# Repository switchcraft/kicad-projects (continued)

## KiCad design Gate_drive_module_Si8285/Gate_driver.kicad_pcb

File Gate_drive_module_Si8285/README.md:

# Gate driver plug-in module Si8285 edition

Gate driver plug-in module for use as a plug-in component on any circuit board
that needs to drive a IGBT, MOSFET, or SiC power transistor.

The Si8285 is a relatively cheap advanced gate drive IC.

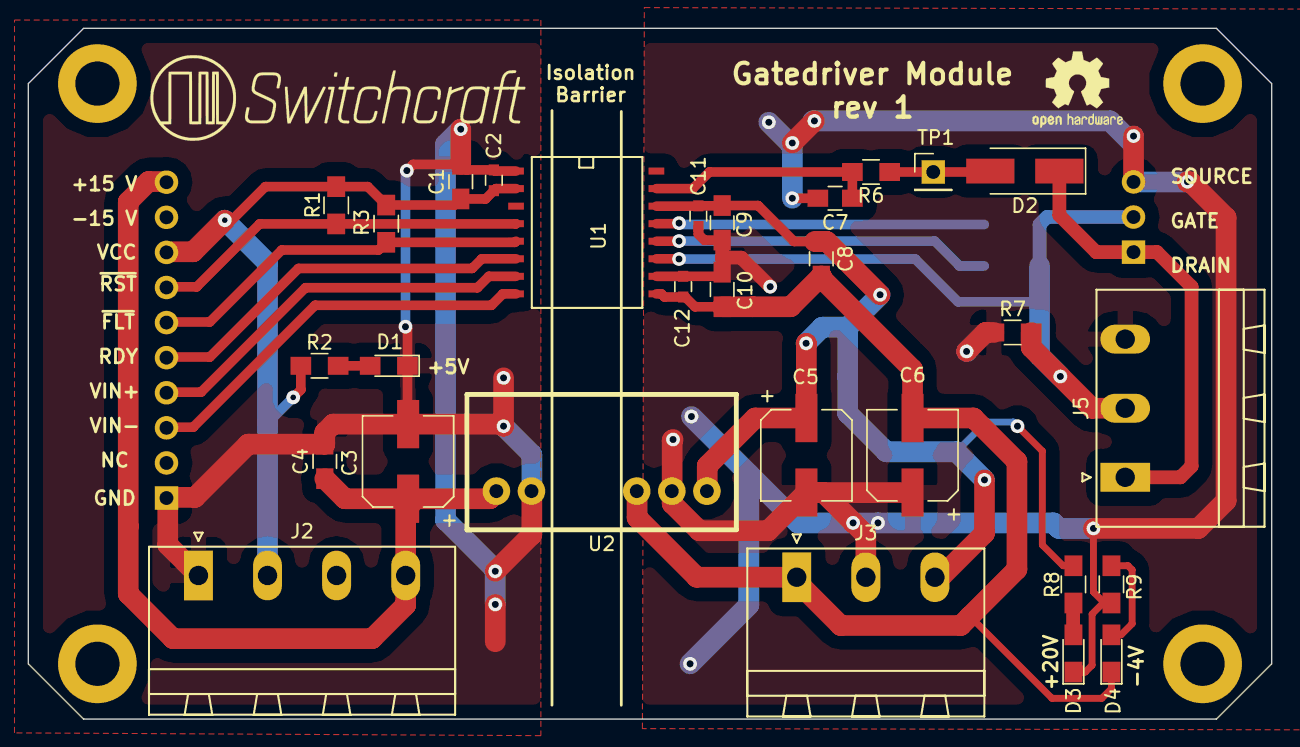
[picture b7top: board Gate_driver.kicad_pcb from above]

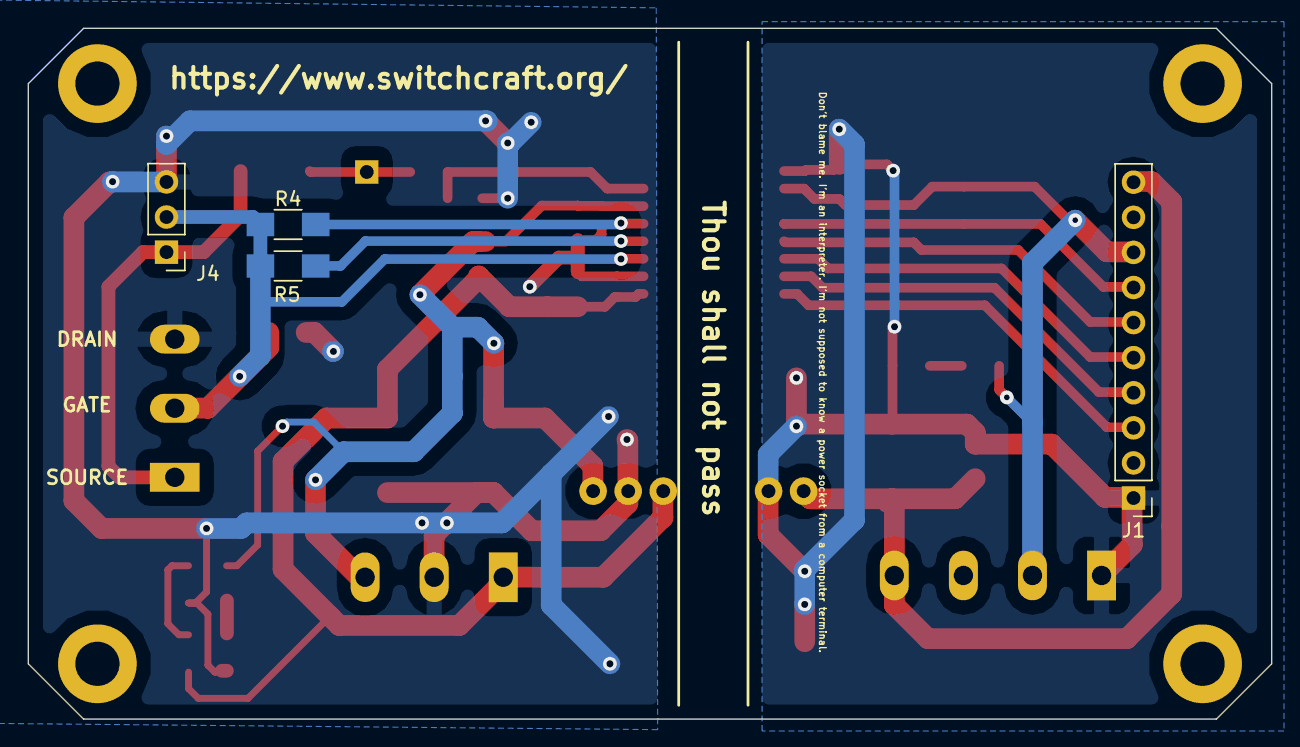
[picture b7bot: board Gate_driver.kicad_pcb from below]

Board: 2 copper layers, 90.0 x 50.0 mm, 33 parts (4 on the bottom side), 20 nets.

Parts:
C1, C8, C9, C10: 10u; C_0805_HandSoldering
C2, C11, C12: 100n; C_0603
C3, C5, C6: 100u; CP_Elec_6.3x7.7
C4: 100n; C_0805_HandSoldering
C7: 390p; C_0805_HandSoldering
D1: RED PWR LED; LED_0805_HandSoldering
D2: ES1F; D_SMA_Handsoldering
D3, D4: GREEN PWR LED; LED_0805_HandSoldering
J1: CONN_01X10; Pin_Header_Straight_1x10_Pitch2.54mm
J2: CONN_01X04; MSTBA_25_4p_G_508-1757268
J3, J5: CONN_01X03; MSTBA_25_3p_G_508-1757488
J4: CONN_01X03; Pin_Header_Straight_1x03_Pitch2.54mm
R1, R2, R3, R8, R9: 10k; R_0805_HandSoldering
R4, R5: 10R; R_1206_HandSoldering
R6: 100R; R_0805_HandSoldering
R7: 100k; R_0805_HandSoldering
TP1: TEST; Pin_Header_Straight_1x01_Pitch2.54mm
U1: Si8285; SO-16-W
U2: Mornsun_QA01C; QA01C

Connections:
+15V: C3.1, C4.1, J1.10, J2.4, U2.1
GND: C1.2, C2.2, C3.2, C4.2, D1.1, J1.1, J2.1, U1.1, U2.2
GND_ISO: C5.2, C6.1, C7.2, C9.2, C10.1, C11.2, C12.1, D3.1, J3.2, J4.3, J5.3, R7.1, R9.1, U1.10, U2.6
unnamed: C7.1, R6.2, U1.15
unnamed: D1.2, R2.2
unnamed: D2.1, J4.1, J5.1
unnamed: D2.2, R6.1, TP1.1
unnamed: D3.2, R8.2
unnamed: D4.2, R9.2
unnamed: J1.3, U1.8
unnamed: J1.4, U1.7
unnamed: J1.5, U1.6
unnamed: J1.6, R3.2, U1.5
unnamed: J1.7, R1.2, U1.4
unnamed: J4.2, J5.2, R4.1, R5.1, R7.2, U1.11
unnamed: R4.2, U1.13
unnamed: R5.2, U1.12
VCC: C1.1, C2.1, J1.8, J2.2, R1.1, R2.1, R3.1, U1.2
VCC_ISO: C5.1, C8.1, C9.1, C11.1, J3.3, R8.1, U1.14, U2.7
VEE_ISO: C6.2, C8.2, C10.2, C12.2, D4.1, J3.1, U1.9, U2.5

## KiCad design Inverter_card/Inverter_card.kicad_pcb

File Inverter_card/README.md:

# Inverter_card

Card for Semikron transistor module card. 

Features connections to gatedrivers and motor output.

This card is designed to sit on top of the DC-link capacitors.

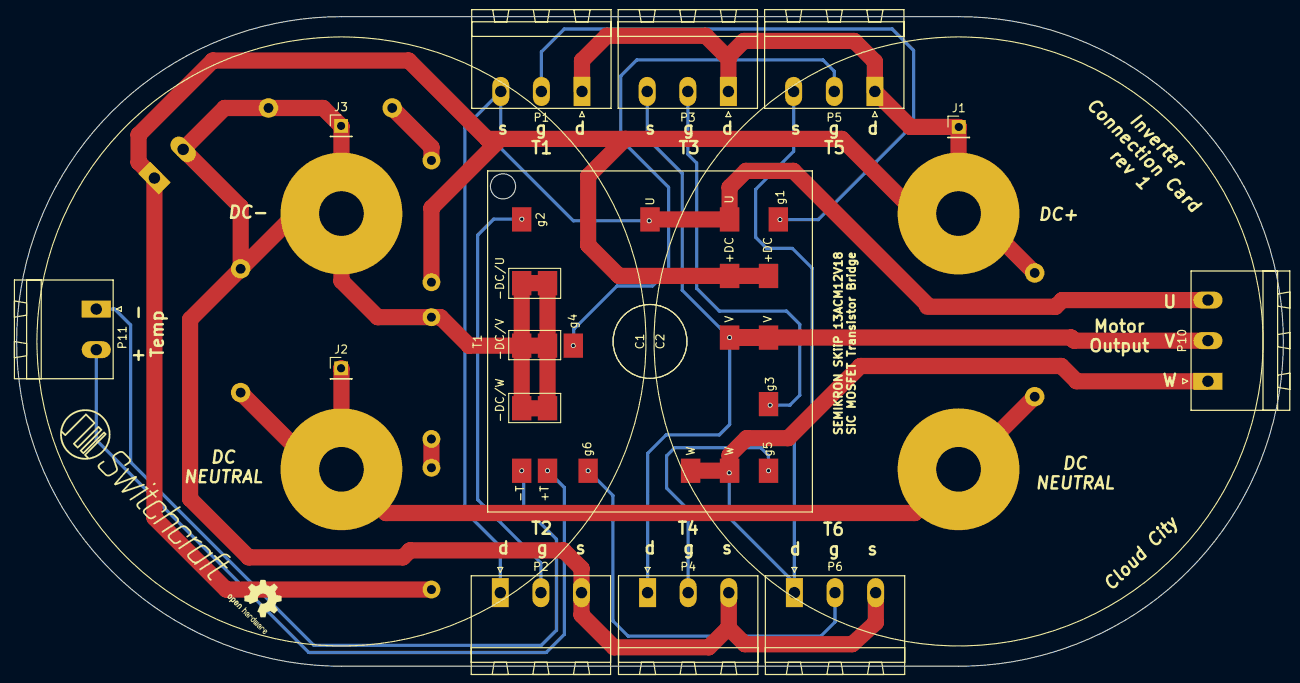
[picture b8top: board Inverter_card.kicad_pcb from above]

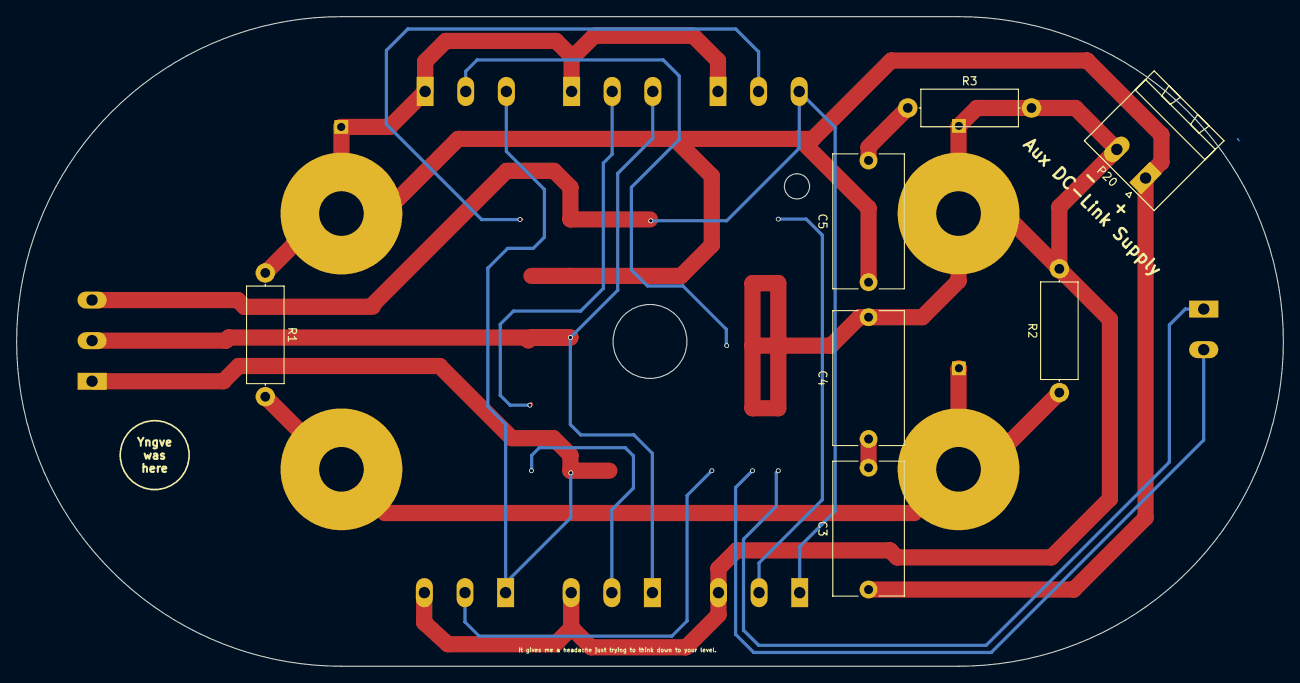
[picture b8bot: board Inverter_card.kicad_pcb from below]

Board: 2 copper layers, 156.0 x 80.0 mm, 21 parts (7 on the bottom side), 16 nets.

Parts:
C1, C2: CP; HCGF6A
C3, C4, C5: C; C_Rect_L16.5mm_W8.7mm_P15.00mm_MKT
J1, J2, J3: CONN_01X01; Pin_Header_Straight_1x01_Pitch2.54mm
P1, P2, P3, P4, P5, P6, P10: CONN_01X03; MSTBA_25_3p_G_508-1757488
P11, P20: CONN_01X02; MSTBA_25_2p_G_508-1757242
R1, R2, R3: R; R_Axial_DIN0414_L11.9mm_D4.5mm_P15.24mm_Horizontal
T1: SemikronSKiiP_13ACM12V18; SKiiP_13ACM12V18

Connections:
DC+: C1.1, C3.1, C5.1, J1.1, P1.1, P3.1, P5.1, P20.1, R1.1, T1.7, T1.8
DC-: C2.2, C4.2, J3.1, P2.3, P4.3, P6.3, P20.2, R2.2, R3.2, T1.9, T1.10, T1.11, T1.12, T1.13, T1.14
unnamed: C1.2, C2.1, J2.1, R1.2, R2.1
unnamed: C3.2, C4.1
unnamed: C5.2, R3.1
unnamed: P11.1, T1.22
unnamed: P11.2, T1.21
T1_g: P1.2, T1.1
T2_g: P2.2, T1.2
T3_g: P3.2, T1.3
T4_g: P5.2, T1.4
T5_g: P4.2, T1.5
T6_g: P6.2, T1.6
U: P1.3, P2.1, P10.3, T1.15, T1.16
V: P3.3, P4.1, P10.2, T1.17, T1.18
W: P5.3, P6.1, P10.1, T1.19, T1.20

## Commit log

2017-07-16 Added existing project files to git
2017-07-16 Added minor changes to readme
2017-07-16 Erase and rewind (restartet repo due to gitignore problems)
2017-07-16 Updated mask
2017-07-16 Initial push of existing project files
2017-07-16 Added project description
2017-07-16 Added readme info about Flyback project
2017-07-16 Added project description in readme.md files
2017-07-16 Set theme jekyll-theme-merlot
2017-07-18 Relative path to layout description file
2017-07-24 First draft of the gate driver circuit
2017-07-24 info about bypass capacitor for HCPL-3120 in schematic
2017-07-28 Added readme
2017-07-28 Added inverter card schematics and PCB
2017-07-28 Started work on front-end card
2017-07-30 Started work on the schematic
2017-07-30 Started working on Diode connection card
2017-07-31 Added protection circuits
2017-07-31 First draft of DC-link controller ready
2017-07-31 Associated some footprints
2017-08-01 Replaced clamping diodes
2017-08-01 New switching transistor
2017-08-01 Redesigned voltage card
2017-08-01 Updated .gitignore to include .kicad_pcb files
2017-08-01 Added all .kicad_pcb files
2017-08-01 Changed resistor value
2017-08-01 Further modifications to volt sensor project (libraries)
2017-08-01 Changed layout description file in pcb-layout
2017-08-01 Updated LEM footprint library
2017-08-01 Updated LEM footprint
2017-08-01 Changed pot meter
2017-08-02 Updated current sensor card
2017-08-02 First draft of gate driver module schematic
2017-08-02 Added additional power and output connector
2017-08-02 Changed interface connector
2017-08-03 Started work on PCB layout
2017-08-03 Updated component value
2017-08-03 Updated footprint for mornsun with 3D model and correct courtyard
2017-08-03 Changed to library path variable
2017-08-03 Fixed 3d shape configuration for cross platform dev. (I hope)
2017-08-03 Created new gate drive revision using Si8285
2017-08-03 PCB layout nearly finished, comments are welcome
2017-08-04 Added edge cuts, logo, mounting holes, dimmensions, silkscreen
2017-08-04 Added more measurements, adjusting screw holes
2017-08-04 Moved silkscreen component names to enhance visibility
2017-08-04 Adjusted Switchcraft logo position
2017-08-04 Minor layout changes
2017-08-04 Moved some footprints
2017-08-04 initial pcb layout
2017-08-04 Added open hardware logo
2017-08-04 Minor cosmetic changes
2017-08-06 Added Texas controller to schematic. Correct symbol ?
2017-08-06 renamed project files
2017-08-06 The LM2587 has a different purpose
2017-08-06 Added some PCB annotations
2017-08-07 Finalized - Ready for production
2017-08-07 Added OSHW-logo
2017-08-08 Added unignored folder "*/gerber/*" to track all manufacturing plot files. E.g. /pcb-name/gerber/*
2017-08-08 Fixed .gitignore to unignore gerber-directory
2017-08-08 Added gerber-plots and drill file
2017-08-08 Made new schematic, started PCB layout
2017-08-08 Minor silkscreen change
2017-08-08 Existing gerber files
2017-08-08 Improved anlog voltage reference
2017-08-08 Replaced DC/DC converter footprint for increased pad size
2017-08-08 Continued work on PCB layout
2017-08-14 Added R out current sensor output. Redesigned and finalized layout
2017-08-15 Corrected library reference to phoenix connectors
2017-08-15 Added final touch to silkscreen
2017-08-15 Production gerbers sent to Seeed
2017-08-17 added missing drill files
2017-08-17 Renamed folders of manufactured PCBs: "[PCB name]_rev1_frozen". Files should now be considered "frozen" and should not be altered. These files and folders are now reference schematics/drawings.
2017-08-18 Revert "Renamed folders of manufactured PCBs: "[PCB name]_rev1_frozen". Files should now be considered "frozen" and should not be altered. These files and folders are now reference schematics/drawing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
    This reverts commit b5649e61b8d6c45365b5dc6287475276ab9b97a7.
2017-09-03 Added component values for bias adjustment
2017-09-03 Added component values
2017-09-03 Updated components
2017-09-08 improved readability of schematic
2017-09-08 Redrawn schematic, added component values and ratings, changed diodes to correct type
2017-09-08 More layout changes and annotation/footprint assosiations
2017-09-20 Added component values as soldered
2017-09-23 Updated minor error in schematic text
2017-10-03 Updated component values and highlighted errors and/or improvement possibilities for next revision
2017-12-09 Edited git-ignore
2017-12-09 Added Inverter_card_2 with updated layout and new current/voltage sensing
2017-12-10 Added DC/DC converter and re-arranged the schematic.
2017-12-10 Updated to inverter_card_2
2017-12-10 Re-arranged DC/DC converter
2017-12-10 Corrected absolute library paths to relative.
2017-12-10 Added more relative paths
2017-12-10 Added LED for isolated output voltage. Re-arranged schematic around isolated op-amp.
2017-12-10 Added capacitor at isolated DCDC output. Removed 1 of 2 series capacitors for both branches at 5V input side.
2017-12-10 Minor rearrangements
2017-12-10 Added some test-points, and bypass capacitors
2017-12-10 Added some additional test-points, and neutral point connection
2017-12-10 New current sense, and iso amp. connector
2017-12-10 Added more test points, changed labels to power ports. Tidyed up a little bit
2017-12-10 Corrected a mistake, moved 5V_iso LED to power supply section instead of voltage measurement section
2017-12-10 Moved resistor connection
2017-12-10 Added ground to temp connector
2017-12-10 Annotated schematic, added most of the footprints, minor re-arrangements.
2017-12-10 Created netlist and spread out footprints on .kicad-pcb file.
2017-12-15 Minor change to .gitignore, and upload of some new projects
2017-12-17 Initial work on inverter card 2 (footprints, layout etc)
2017-12-22 New commit of production batch 1
2018-03-04 Added on-delay PCB for pre-charge controller
2018-03-04 Updated library path
2018-03-04 Initial project for thyristor based DC-motor drive
2018-08-08 Removed some hard-coded paths
2018-08-08 Removed hard-coded paths
2018-09-07 A lot of work on InverterCard 2.0 pcb layout
2018-09-07 More adjustments to PCB
2018-09-07 Added Farnell_ID to components (order information). Decided snubber caps.
2018-09-08 Created new project: FrontEnd-Inverter. A card with both rectifier, inverter and sensing for voltage and current.
2018-09-08 Further work on layout
2018-09-17 Minor adjustments on tracks and traces.
2018-09-18 Modified paths in order to make project portable
2018-09-22 added sym-lib-table (project specific lib files) as .gitignore was updated.
2018-09-22 Updated schematic with single 20x2 pinsocket instead of 6 pcs 3x1 pinheaders for gate driver connections
2018-09-22 Further work on pcb layout: new pinsocket + enlarged tracks for low voltage signals
2018-09-22 Further work on increasing zone area and track width
2018-09-22 Tweaking position of snubber components C7 and R7 to get closer to DC+ at inverter module T1. Work in progress.
2018-09-23 Initial commit of new gate driver design (not a finished design)
2018-09-23 Finalized C7 and R7 placement. Started improving gatedriver connection with zones and vias.
2018-09-25 Improved tracks from inverter module to pinsocket
2018-12-20 Changed current sensor. Work in progress.
2018-12-22 Further work on inverter card schematic; added ACS720 sensors and started implementing connector symbols for communication of measurements and firing signals
2018-12-23 Implemented the new symbol for dual gatedriver control (connector). Added 3V3 input. Made things tidy.
2019-01-02 Further work on Inverter card. Schematic mostly done - still working on layout.
2019-01-02 Fixed bug in DC+ supply to T1
2019-01-02 further adjustments to pcb layout.
2019-01-06 Updated connector type for brake chopper gatedriver connection from GMSTBA to 2.54mm pin header. More work with tracks and zones on PCB layout.
